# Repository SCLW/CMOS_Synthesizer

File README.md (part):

# CMOS Sound Experimentation Board

*CMOS Sound Experimentation Board. Photo: © Yunfei Zhang.*

## About this project

The board is both a teaching tool and a performance instrument: a low-threshold way to explore audio electronics and logic concepts while also functioning as a working sound source in artistic practice. Inexpensive 4000-series CMOS logic ICs, originally developed for general-purpose digital electronics such as calculators, digital clocks, timing circuits, and industrial control, serve as the sound generators, brought together on a single patchable interface that exposes rather than hides the signal flow. Although the signals are limited to square waves, with no envelopes, no MIDI, and no DSP, the board produces a wide range of sounds and sonic textures.

It was developed within the [Circuitry-Based Sound](https://github.com/SCLW/Circuitry-Based-Sound) seminar at HfG Karlsruhe as part of an ongoing inquiry into how self-built electronics shape experimental sound, collective performance, and arts pedagogy. Many boards have been built, modified, and played in ensemble settings and workshops. That repository documents the broader tradition of CMOS-based sound, related literature, and the underlying electronics.

Technically, the board integrates discrete 4000-series CMOS logic chips on a single PCB that also functions as the user interface. The chips operate as square-wave oscillators, frequency dividers, sequencers, modulators, noise sources, and pattern generators. Prewired connections, selectable switches, and patchable female headers and sockets let users interconnect logic-level signals with jumper wires to explore rhythmic structures, grainy textures, drones, glitches, and complex noise patterns.

---

| **Project Title**     | CMOS Sound Experimentation Board                                                                                                            |
| :-------------------- | :------------------------------------------------------------------------------------------------------------------------------------------ |
| **Hardware Version**      | 2.0 (Rev B; complete 2024 redesign of an earlier 2020 prototype now superseded)                                                   |
| **Documentation Release** | v1.0.0 (first archived release of this repository)                                                                                      |
| **Author / Designer** | Lorenz Schwarz                                                                                                                              |
| **Status**            | Completed                                                                                                                                   |
| **Start Date**        | April 2024                                                                                                                                  |
| **Completion Date**   | May 2024                                                                                                                                    |
| **License**           | [CC BY 4.0](https://creativecommons.org/licenses/by/4.0/)                                                                                   |
| **Description**       | A modular experiment board built around 4000-series CMOS logic chips for sound generation, musical interaction, and circuit-based learning. |
| **Hardware**          | CMOS logic ICs (4000-series), analog multiplexers, potentiometers, slide and rotary switches                                                |
| **Keywords**          | single-PCB, patchable CMOS instrument, educational electronics, experimental sound, logic circuits                                          |

---

## About this documentation

This repository contains all the files and instructions required to build, study, or modify the CMOS Sound Experimentation Board:

- **PCB design files and schematics** (EAGLE)  
- **Assembly and mechanical drawings**  
- **Bill of Materials (BOM)**  
- **Reference tables and component data sheets**

Anyone is free to reproduce, adapt, or extend the instrument for artistic work, performance, or research.

## The instrument

The instrument is designed for hands-on use. Its circuits are prewired for immediate operation but can also be manually interconnected to create new signal paths. All major inputs and outputs are broken out to female headers, allowing flexible patching with male-to-male jumper wires. Global I/O connections make it possible to chain multiple boards together.

The instrument has been used in university seminars, collective performances, and collaborations between electronic and acoustic musicians, from workshops in Langa (Cape Town) to performances at the ZKM Karlsruhe.

*This project is part of the ongoing teaching and research initiative [**Circuitry-Based Sound**](https://github.com/SCLW/Circuitry-Based-Sound) at the HfG Karlsruhe, which explores the relationship between electronic circuitry, interaction, and sound.*

*CMOS Sound Experimentation Board. Photo: © Tobias Ehrhardt.*

## Performances and contexts of use

The board has been used as a shared platform across the Circuitry-Based Sound programme since 2024, including:

- **ng X, next_generation X festival**, ZKM, Karlsruhe (2024)
- **Workshop with Dizu Plaatjies**, Langa, Cape Town, South Africa (2024)
- **Bowed Electrons / IMMP**, !Khwa ttu San Heritage Centre, South Africa (2024)
- **Open M Art Fair**, OōEli Hangzhou Tianmuli, Hangzhou (2025)
- **SAE Cape Town workshop**, Cape Town, South Africa (2025)
- **MKULTRA Sound 2026**, HfG Karlsruhe (2026)

Boards built by participants have been used in solo and ensemble configurations, patched together via the chained clock and external-input headers. Demo video and context: <https://medienkunst-sound.de/works/cmos-synthesizer>.

---

*Circuitry-Based Sound participants preparing for the* next_generation X *festival performance in the ZKM Klangdom, Karlsruhe, 2024. Photo: © Hongyu Guo.*

<br>

*Workshop with Dizu Plaatjies in Langa, Cape Town, South Africa, 2024. Participants assemble and patch their CMOS Sound Experimentation Boards through portable amplifiers. Photo: © Paul Modler.*

<br>

*Bowed Electrons / IMMP, !Khwa ttu San Heritage Centre, South Africa, 2024. A performer operates the CMOS Sound Experimentation Board during the concert; other musicians prepare in the background. Photo: © Clive Pringle.*

<br>

*Visitors inspecting the CMOS Sound Experimentation Board at the Open M Art Fair, OōEli Hangzhou Tianmuli, China, 2025. Photo: © Yunfei Zhang.*

<br>

*Circuitry-Based Sound workshop at SAE Cape Town, with participants working on the boards, 2025. Photo: © Paul Modler.*

<br>

*MKULTRA Sound 2026, audiovisual performance by Yunfei Zhang and Xinyun Zhang at HfG Karlsruhe, February 2026. The board controls a hacked VGA video signal generator while simultaneously functioning as a sound source. Photo: © Jihye Gebhart.*

<br>

*Live-generated VGA visual projected on a wall at HfG Karlsruhe during the same MKULTRA Sound 2026 performance by Xinyun Zhang and Yunfei Zhang. Photo: © Jihye Gebhart.*

## Disclaimer

This material is for educational and research purposes. Although prepared with care, errors may remain. Building this synthesizer may require additional knowledge/experience in electronics and prototyping. The materials are provided to encourage exploration and adaptation.

---

### Specifications

- **PCB:** custom 2-layer board
- **Dimensions (Board):** 278 mm × 186 mm  
- **Dimensions (Populated + Base Plate):** 284 mm × 192 mm × 35 mm
- **Power Requirements:** Operating range 9–18 V DC; recommended 9–12 V (typical 9 V battery). The oscillator frequency-range table in the [Appendix](#appendix) is calibrated at 10 V.
- **Component Types:**
  - **ICs:** CMOS 4000-series; mix of SMD and through-hole
  - **Passives:** SMD resistors (0805), SMD ceramic/electrolytic capacitors
  - **Electromechanical:** vertical PCB-mount potentiometers; slide/rotary switches (THT); 2.54 mm pin headers & sockets
- **Audio:**
  - Mono output, ~4 Vpp typical; up to synth/modular level with gains fully open
  - Master output pot provides attenuation toward line level
- **Connectors:**
  - **Power in:** 2-pin male header (2.54 mm); polarity marked on PCB silkscreen; mating cable: 2-pos female socket → wire leads (~600 mm)
  - **Audio out:** 3.5 mm mono jack
  - **Expansion/control:** 2.54 mm female headers (various pin counts) for patching

---

## Circuit Elements on the CMOS Sound Experimentation Board

The board integrates a wide range of CMOS logic-based sound circuits, allowing direct experimentation with square-wave oscillators, counters, modulators, sequencers, and switches. All elements are accessible via female headers and can be interconnected using jumper wires to create complex rhythmic and sonic structures.

In total the board offers up to **13 oscillator positions**: 8 gated oscillators based on CD4093 (sections 1–8 below), 4 sensor-input oscillators based on CD40106 (sections 9–12), and 1 master clock (also CD40106, described as its own section).

<picture>
  <source media="(prefers-color-scheme: dark)" srcset="/assets/img/overlay-functions-dark.svg">
  
</picture>

Functional diagram of the CMOS Sound Experimentation Board, showing the main circuit sections and their interconnections.

### GATED OSCILLATORS 1-8 [2×]

Each of the two sections contains four gated Schmitt-trigger oscillators based on the CD4093 NAND gate IC.
These circuits generate square-wave signals, each with its own frequency potentiometer, range selector, and logic gate input for gating or modulation.

### XOR MODULATOR [2×]

Two XOR-based square-wave modulators (CD4070) for logical ring modulation to create new harmonic relationships. Each modulated output is individually accessible and can be patched into other sections.

### SWITCH 1 OF 8 [2×]

Two CD4051 analog MUX/DEMUX sections acting as 1-of-8 selectors. Selection via three logic inputs, optionally driven by a CD4024 binary counter (0–7) to step through the switch positions automatically. The switch operates bidirectionally: it can either route one signal to one of eight destinations or select one of eight inputs to a common output.

### SWITCH 3 × 1 OF 2 [1×]

Built around a CD4053 triple SPDT analog switch, this circuit provides three independent 2-channel selectors. Each channel can switch between two input signals under binary logic control, which requires an additional logic control input. The switch operates bidirectionally: it can either route one signal to one of two destinations or select one of two inputs to a common output.

### FREQUENCY DIVIDER [2×]

Two 7-stage binary counters (CD4024) used as binary number generators (÷2…÷128). One pre-clocked from gated oscillator #8; the other can receive any selectable clock source via a rotary switch.

### SEQUENCER/COUNTER [1×]

Based on CD4022, an 8-stage Johnson counter acting as a step sequencer. It outputs sequential logic pulses across eight decoded outputs and includes a reset function. The sequencer clock can be selected via a rotary switch.

### DIVIDE BY 3, 5, 7, 9 [1×]

A divide-by-odd “pattern generator” implemented using CD4018 and CD4011. It generates rhythmic subdivisions by dividing the input clock into odd-numbered ratios (÷3, ÷5, ÷7, ÷9). The clock source is selectable through one of the rotary switches.

### OSCILLATORS 9–12

Four auxiliary Schmitt-trigger oscillators (CD40106) with sockets for touch, light-dependent, or resistive sensors. These share the same CD40106 IC as the master clock (see [Clock](#clock-1) below); inserting a variable resistor or sensor into the open pads activates each oscillator.

### CLOCK [1×]

One of the CD40106 Schmitt trigger inverters is configured as the master clock oscillator. The clock signal is routed via the rotary switches, allowing it to be assigned as a timing source to different logic sections, and can additionally be sent to an external output for synchronization between multiple boards.

### PSEUDO RANDOM NUMBER GENERATOR [1×]

Based on three interconnected CD4094 shift registers (24 stages) forming a linear-feedback shift register (LFSR). The circuit generates pseudo-random bit patterns and requires an additional adapter board for seeding and deadlock-prevention circuit using CD4068, CD4070, and CD4077 to ensure continuous operation. See [LFSR Deadlock Prevention Circuit](#lfsr-deadlock-prevention-circuit-required). The clock source can be selected via one of the rotary switches.

### MIXER [1×]

4-channel summing amplifier (LM358) with per-channel gain and master level. The mixed signal is available as mono output.

### ROTARY SWITCHES [3x]

Three Single Pole, 8-Throw rotary switches (SP8T) provide manual routing of oscillator and clock signals to different logic sections. Each switch selects one of eight possible sources, allowing flexible assignment of timing and modulation signals across the system.

| **Position** | **Source**       |
| :----------: | :--------------- |
|       1      | OSC1             |
|       2      | OSC2             |
|       3      | OSC3             |
|       4      | OSC4             |
|       5      | Master Clock     |
|       6      | OSC8 ÷ 4         |
|       7      | External Input 1 |
|       8      | External Input 2 |

---

## Schematics & design files

Complete circuit schematics (PDF) for all sections are in [`/assets/exports/`](./assets/exports/).  
Editable EAGLE design files are in [`/assets/pcb/`](./assets/pcb/).  
For a browsable SVG overview that links to PDFs, see [`/assets/exports/README.md`](./assets/exports/README.md).

> **Note on EAGLE.** The `.brd` and `.sch` files were created with Autodesk EAGLE (last standalone release 9.6.2, now discontinued). They can still be opened in Autodesk Fusion's Electronics workspace, or imported into KiCad via its built-in EAGLE importer.

## Build guide

The main PCB integrates all control elements (potentiometers, toggle switches, tactile buttons) directly. No separate front panel or off-board wiring is needed. One auxiliary add-on PCB prevents LFSR deadlock and mounts directly on the main board; see [LFSR Deadlock Prevention Circuit](#lfsr-deadlock-prevention-circuit-required).

## The main board

*CAM top view of the main board showing component outlines, silkscreen labels and pad holes.*  

**Main Board with component outline**  

*Top view of the main PCB showing component outlines and mounting holes. This overlay provides a visual reference for component placement.*

<details>

<summary>PCB Reference Designators and Component List, main board (click to expand)</summary>

> This table lists the components for the **main board only**. The LFSR deadlock-prevention add-on has its own component list further down ([here](#lfsr-deadlock-prevention-circuit-required)) and its own entry in the [BOM file](/assets/bom/README.md#lfsr-deadlock-prevention-add-on-board).

| Qty    | Value          | Package     | Designators                                         | Description                                  |
| ------ | -------------- | ----------- | --------------------------------------------------- | -------------------------------------------- |
| 1      | 1 kΩ           | R0805       | R23                                                 | SMD Resistor                                 |
| 10     | 2.7 kΩ         | R0805       | R1–R8, R13, R15                                     | SMD Resistor                                 |
| 1      | 150 kΩ         | R0805       | R26                                                 | SMD Resistor                                 |
| 7      | 10 kΩ          | R0805       | R14, R16–R20, R27                                   | SMD Resistor                                 |
| 8      | 100 kΩ         | R0805       | R9–R12, R21–R22, R24–R25                            | SMD Resistor                                 |
| 15     | 10 µF          | PANASONIC_D | C1–C7, C12–C13, C23, C49–C53                        | Electrolytic Capacitor (SMD; C23 optional, depends on master-clock timing choice) |
| 36     | 0.1 µF         | C0805       | C8–C11, C14–C17, C18–C22, C24–C29, C31–C41, C43–C48 | SMD Ceramic Capacitor                        |
| 14     | 100 kΩ         | POT_VER     | U$1–U$14                                            | Potentiometer, vertical                      |
| 2      | —              |             | S12–S13                                             | Tactile pushbutton (momentary, SMD)          |
| 8      | —              | THT         | S1–S8                                               | Toggle Switch, ON–ON                         |
| 1      | CD40106        | DIL14       | IC13                                                | Hex Schmitt Trigger Inverter                 |
| 1      | CD4011         | DIL14       | IC12                                                | Quad 2-input NAND                            |
| 1      | CD4018         | DIL16       | IC11                                                | Counter / Divider                            |
| 1      | CD4022         | DIL16       | IC9                                                 | Divide-by-8 Counter                          |
| 2      | CD4024         | DIL14       | IC6, IC8                                            | 7-stage Binary / Ripple Counter              |
| 2      | CD4051         | DIL16       | IC2, IC5                                            | 8-channel Analog Multiplexer                 |
| 1      | CD4053         | DIL16       | IC7                                                 | Triple 2-channel Analog Multiplexer          |
| 2      | CD4070         | DIL14       | IC4, IC14 (IC18 unpopulated)                        | Quad 2-input XOR                             |
| 2      | CD4093         | DIL14       | IC1, IC3                                            | Quad 2-input NAND Schmitt Trigger            |
| 3      | CD4094         | DIL16       | IC15–IC17                                           | 8-stage Shift Register                       |
| 1      | LM358          | DIL08       | IC10                                                | Dual Operational Amplifier                   |
| 1      | MBRS1540       |             | D1                                                  | Schottky Protection Diode (1.5 A / 40 V)     |
| 1      | MJ-3523-SMT-TR | SMD         | —                                                   | Female Jack Connector, 3.5 mm, surface-mount |
| 3      | —              | ROTARY      | S9–S11                                              | Rotary Switch                                |
| 8      | —              | DIL14       | —                                                   | IC Socket                                    |
| 1      | —              | DIL08       | —                                                   | IC Socket                                    |
| 8      | —              | DIL16       | —                                                   | IC Socket                                    |
| 5      | —              | 1×8 2.54    | —                                                   | Female Header                                |
| 2      | —              | 1×3 2.54    | —                                                   | Female Header                                |
| 1      | —              | 1×6 2.54    | —                                                   | Female Header                                |
| 6      | —              | 1×2 2.54    | —                                                   | Female Header                                |
| 1      | —              | 1×5 2.54    | —                                                   | Female Header                                |
| 2      | —              | 1×7 2.54    | —                                                   | Female Header                                |
| 11     | —              | 1×4 2.54    | —                                                   | Female Header                                |
| 1      | —              | 1×9 2.54    | —                                                   | Female Header                                |
| 4      | —              | 2×4 2.54    | —                                                   | Female Header                                |
| 1      | —              | 2×3 2.54    | —                                                   | Female Header                                |
| 4      | —              | 1×2 2.54    | —                                                   | Pin Header (Male)                            |

C1, C3–C7, C8–C11, C12–C13, C14–C17, C18–C21, C23, and C25–C29 act as timing capacitors for the Schmitt-trigger RC oscillators in combination with their corresponding resistors. These values can be substituted to tailor the oscillator frequency ranges (see frequency table).

</details>

### Assembly order

The following is a suggested sequence that outlines the build order without step-by-step detail. Refer to the schematics in `/assets/exports/` and the board overlays above for orientation and placement.

1. **Main PCB**
   1) SMD resistors  
   2) SMD capacitors (see [Appendix](#appendix))  
   3) IC sockets  
   4) ICs  
   5) Controls (potentiometers & switches)  
   6) Connectors (2.54 mm headers & sockets)

   **Important:** Do not solder the headers on the main board where the LFSR deadlock-prevention adapter will later be mounted. Solder these headers only on the adapter board, then plug into the main board.

2. **Audio output adapter (obsolete)**
   - For historical reference only; no longer required for audio output in 2024 revision.

3. **Deadlock prevention board for PRNG/LFSR circuit (required)**
   - Three 1×8 female headers + one 1×3 female header to the main board  
   - Two additional wires for VCC and GND

4. **Mechanical assembly**
   - Mount main PCB on acrylic base plate using 8 spacers and M3 screws  

## Modifications and add-on boards

### Audio output adapter (obsolete)
Earlier revisions required a small mono audio adapter (SMT 3.5 mm jack on a daughterboard).  
In the 2024 revision B, the audio section is fixed on the main PCB.

### LFSR Deadlock Prevention Circuit (required)

*CAM top view of the deadlock prevention add-on PCB.*

The LFSR can lock in an all-ones state. A small SMD add-on (CD4068, CD4070, CD4077) detects the static state and injects a seed pulse. It connects to the main board via three 1×8 and one 1×3 female headers, and requires two additional wires for power (VCC and GND).

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
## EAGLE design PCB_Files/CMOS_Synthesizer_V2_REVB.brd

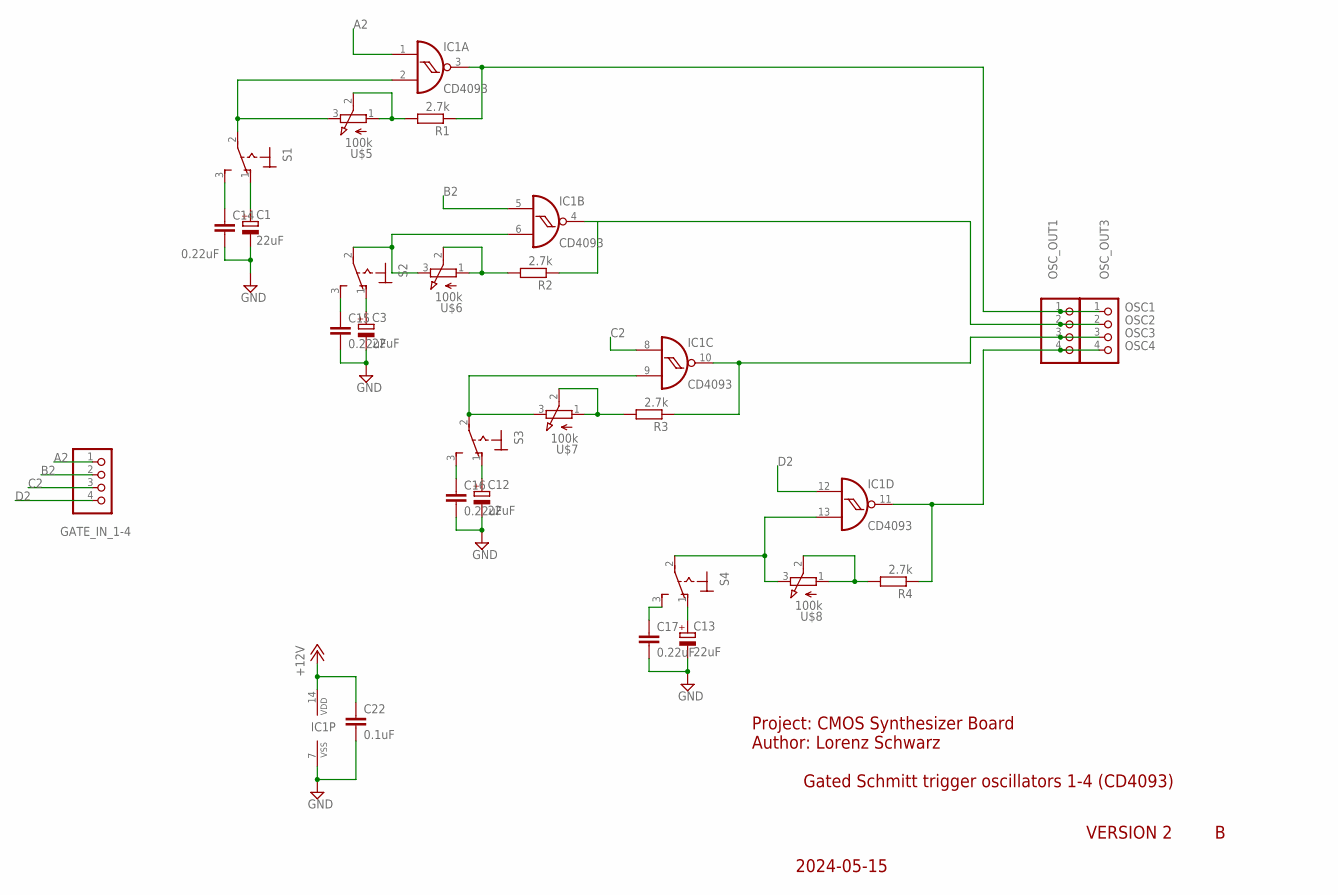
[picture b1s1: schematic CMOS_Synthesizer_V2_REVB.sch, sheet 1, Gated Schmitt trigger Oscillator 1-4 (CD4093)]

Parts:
C1, C3, C12, C13: 22uF; PANASONIC_D
C14, C15, C16, C17: 0.22uF; C0805
C22: 0.1uF; C0805
GATE_IN_1-4: PINHD-1X4_2.54; 1X04
IC1: CD4093; DIL14
OSC_OUT1, OSC_OUT3: PINHD-1X4_2.54; 1X04
R1, R2, R3, R4: 2.7k; R0805
S1, S2, S3, S4: M9040P
U$5, U$6, U$7, U$8: 100k; POT_VER

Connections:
+12V: C22.1, IC1.14 (VDD); also elsewhere on the board
A2: GATE_IN_1-4.1, IC1.1 (I0)
B2: GATE_IN_1-4.2, IC1.5 (I0)
C2: GATE_IN_1-4.3, IC1.8 (I0)
D2: GATE_IN_1-4.4, IC1.12 (I0)
GND: C1.-, C3.-, C12.-, C13.-, C14.2, C15.2, C16.2, C17.2, C22.2, IC1.7 (VSS); also elsewhere on the board
unnamed: C1.+, S1.1 (O)
unnamed: IC1.2 (I1), S1.2, U$5.3 (E)
unnamed: C3.+, S2.1 (O)
unnamed: C15.1, S2.3 (S)
unnamed: IC1.6 (I1), S2.2, U$6.3 (E)
unnamed: C12.+, S3.1 (O)
unnamed: C16.1, S3.3 (S)
unnamed: IC1.9 (I1), S3.2, U$7.3 (E)
unnamed: C13.+, S4.1 (O)
unnamed: C17.1, S4.3 (S)
unnamed: IC1.13 (I1), S4.2, U$8.3 (E)
unnamed: R1.2, U$5.1 (A), U$5.2 (S)
unnamed: R2.2, U$6.1 (A), U$6.2 (S)
unnamed: R3.2, U$7.1 (A), U$7.2 (S)
unnamed: R4.2, U$8.1 (A), U$8.2 (S)
unnamed: C14.1, S1.3 (S)
OSC1: IC1.3 (O), OSC_OUT1.1, OSC_OUT3.1, R1.1; also elsewhere on the board
OSC2: IC1.4 (O), OSC_OUT1.2, OSC_OUT3.2, R2.1; also elsewhere on the board
OSC3: IC1.10 (O), OSC_OUT1.3, OSC_OUT3.3, R3.1; also elsewhere on the board
OSC4: IC1.11 (O), OSC_OUT1.4, OSC_OUT3.4, R4.1; also elsewhere on the board

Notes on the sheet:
Project: CMOS Synthesizer Board Author: Lorenz Schwarz
Gated Schmitt trigger oscillators 1-4 (CD4093)
2024-05-15
VERSION 2

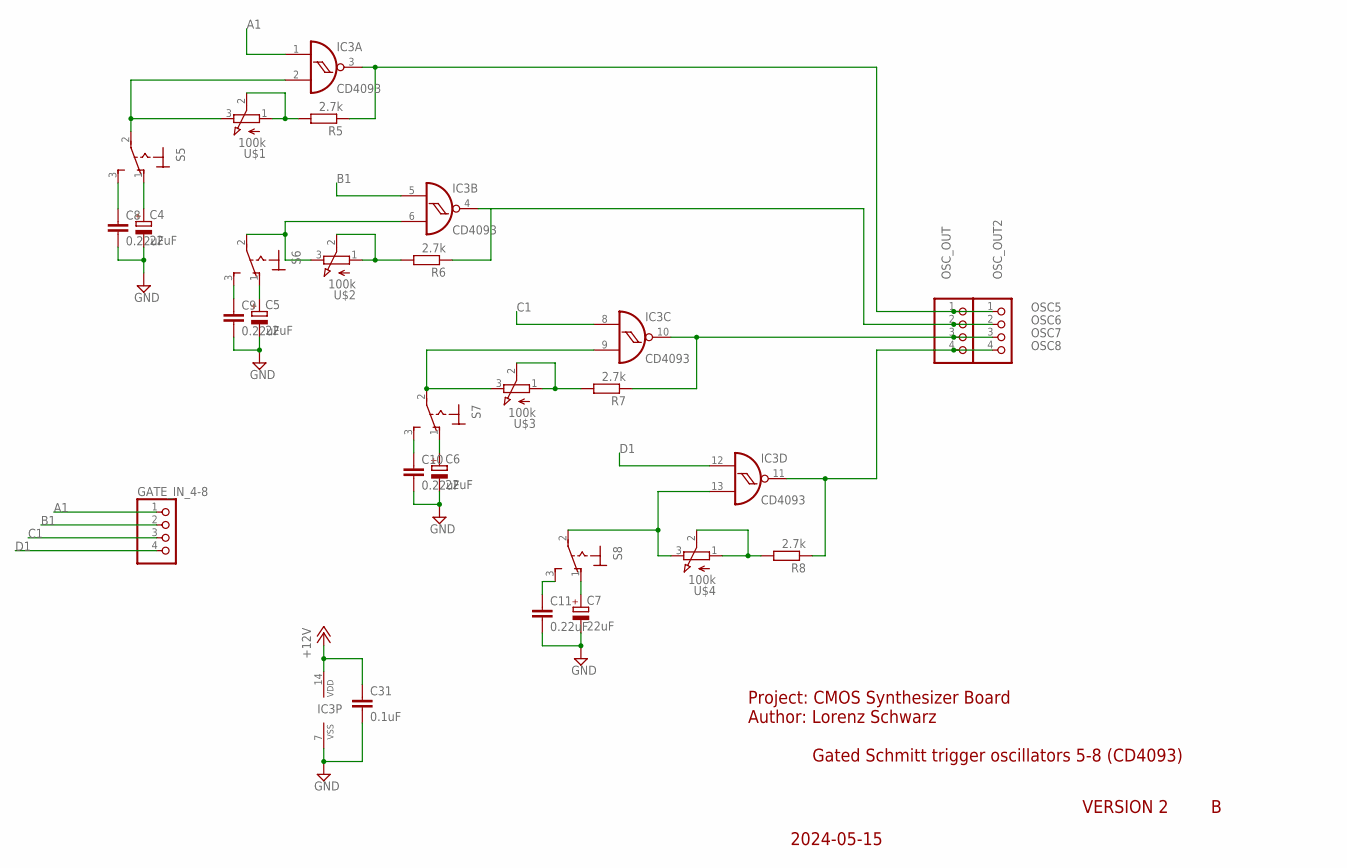
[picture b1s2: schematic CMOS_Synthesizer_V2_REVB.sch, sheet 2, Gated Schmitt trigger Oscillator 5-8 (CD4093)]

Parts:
C4, C5, C6, C7: 22uF; PANASONIC_D
C8, C9, C10, C11: 0.22uF; C0805
C31: 0.1uF; C0805
GATE_IN_4-8: PINHD-1X4_2.54; 1X04
IC3: CD4093; DIL14
OSC_OUT, OSC_OUT2: PINHD-1X4_2.54; 1X04
R5, R6, R7, R8: 2.7k; R0805
S5, S6, S7, S8: M9040P
U$1, U$2, U$3, U$4: 100k; POT_VER

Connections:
+12V: C31.1, IC3.14 (VDD); also elsewhere on the board
A1: GATE_IN_4-8.1, IC3.1 (I0)
B1: GATE_IN_4-8.2, IC3.5 (I0)
C1: GATE_IN_4-8.3, IC3.8 (I0)
D1: GATE_IN_4-8.4, IC3.12 (I0)
GND: C4.-, C5.-, C6.-, C7.-, C8.2, C9.2, C10.2, C11.2, C31.2, IC3.7 (VSS); also elsewhere on the board
unnamed: C5.+, S6.1 (O)
unnamed: C9.1, S6.3 (S)
unnamed: C8.1, S5.3 (S)
unnamed: C4.+, S5.1 (O)
unnamed: IC3.2 (I1), S5.2, U$1.3 (E)
unnamed: IC3.6 (I1), S6.2, U$2.3 (E)
unnamed: C6.+, S7.1 (O)
unnamed: C10.1, S7.3 (S)
unnamed: IC3.9 (I1), S7.2, U$3.3 (E)
unnamed: C7.+, S8.1 (O)
unnamed: C11.1, S8.3 (S)
unnamed: IC3.13 (I1), S8.2, U$4.3 (E)
unnamed: R5.2, U$1.1 (A), U$1.2 (S)
unnamed: R6.2, U$2.1 (A), U$2.2 (S)
unnamed: R7.2, U$3.1 (A), U$3.2 (S)
unnamed: R8.2, U$4.1 (A), U$4.2 (S)
OSC5: IC3.3 (O), OSC_OUT.1, OSC_OUT2.1, R5.1
OSC6: IC3.4 (O), OSC_OUT.2, OSC_OUT2.2, R6.1
OSC7: IC3.10 (O), OSC_OUT.3, OSC_OUT2.3, R7.1
OSC8: IC3.11 (O), OSC_OUT.4, OSC_OUT2.4, R8.1; also elsewhere on the board

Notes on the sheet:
Project: CMOS Synthesizer Board Author: Lorenz Schwarz
Gated Schmitt trigger oscillators 5-8 (CD4093)
2024-05-15
VERSION 2

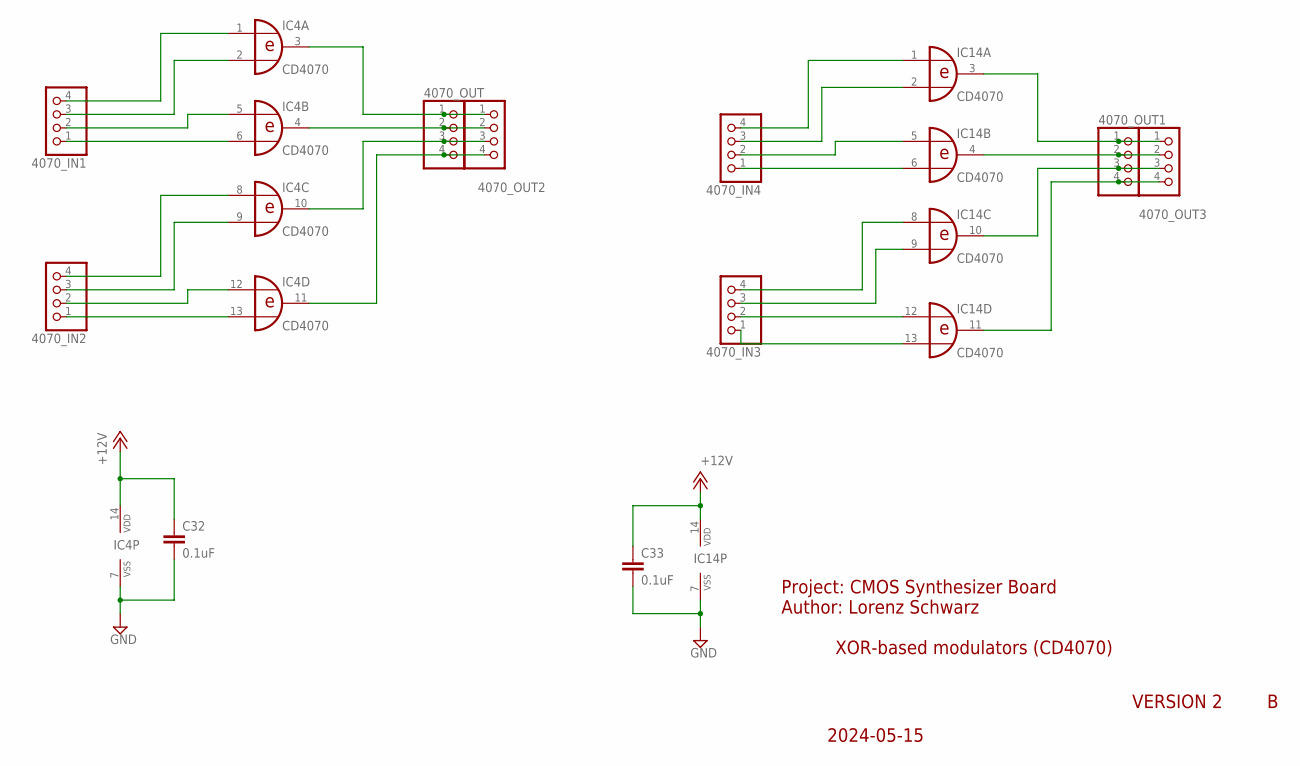
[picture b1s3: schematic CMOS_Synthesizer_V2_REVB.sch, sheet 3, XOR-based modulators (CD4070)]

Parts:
4070_IN1, 4070_IN2, 4070_IN3, 4070_IN4, 4070_OUT, 4070_OUT1, 4070_OUT2, 4070_OUT3: PINHD-1X4_2.54; 1X04
C32, C33: 0.1uF; C0805
IC4, IC14: CD4070; DIL14

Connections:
+12V: C32.1, C33.1, IC4.14 (VDD), IC14.14 (VDD); also elsewhere on the board
GND: C32.2, C33.2, IC4.7 (VSS), IC14.7 (VSS); also elsewhere on the board
unnamed: 4070_OUT.1, 4070_OUT2.1, IC4.3 (O)
unnamed: 4070_OUT.2, 4070_OUT2.2, IC4.4 (O)
unnamed: 4070_OUT.3, 4070_OUT2.3, IC4.10 (O)
unnamed: 4070_OUT.4, 4070_OUT2.4, IC4.11 (O)
unnamed: 4070_IN1.4, IC4.1 (I0)
unnamed: 4070_IN1.3, IC4.2 (I1)
unnamed: 4070_IN1.2, IC4.5 (I0)
unnamed: 4070_IN1.1, IC4.6 (I1)
unnamed: 4070_IN2.4, IC4.8 (I0)
unnamed: 4070_IN2.3, IC4.9 (I1)
unnamed: 4070_IN2.2, IC4.12 (I0)
unnamed: 4070_IN2.1, IC4.13 (I1)
unnamed: 4070_OUT1.1, 4070_OUT3.1, IC14.3 (O)
unnamed: 4070_OUT1.2, 4070_OUT3.2, IC14.4 (O)
unnamed: 4070_OUT1.3, 4070_OUT3.3, IC14.10 (O)
unnamed: 4070_OUT1.4, 4070_OUT3.4, IC14.11 (O)
unnamed: 4070_IN4.4, IC14.1 (I0)
unnamed: 4070_IN4.3, IC14.2 (I1)
unnamed: 4070_IN4.2, IC14.5 (I0)
unnamed: 4070_IN4.1, IC14.6 (I1)
unnamed: 4070_IN3.4, IC14.8 (I0)
unnamed: 4070_IN3.3, IC14.9 (I1)
unnamed: 4070_IN3.2, IC14.12 (I0)
unnamed: 4070_IN3.1, IC14.13 (I1)

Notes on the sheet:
Project: CMOS Synthesizer Board Author: Lorenz Schwarz
XOR-based modulators (CD4070)
2024-05-15
VERSION 2

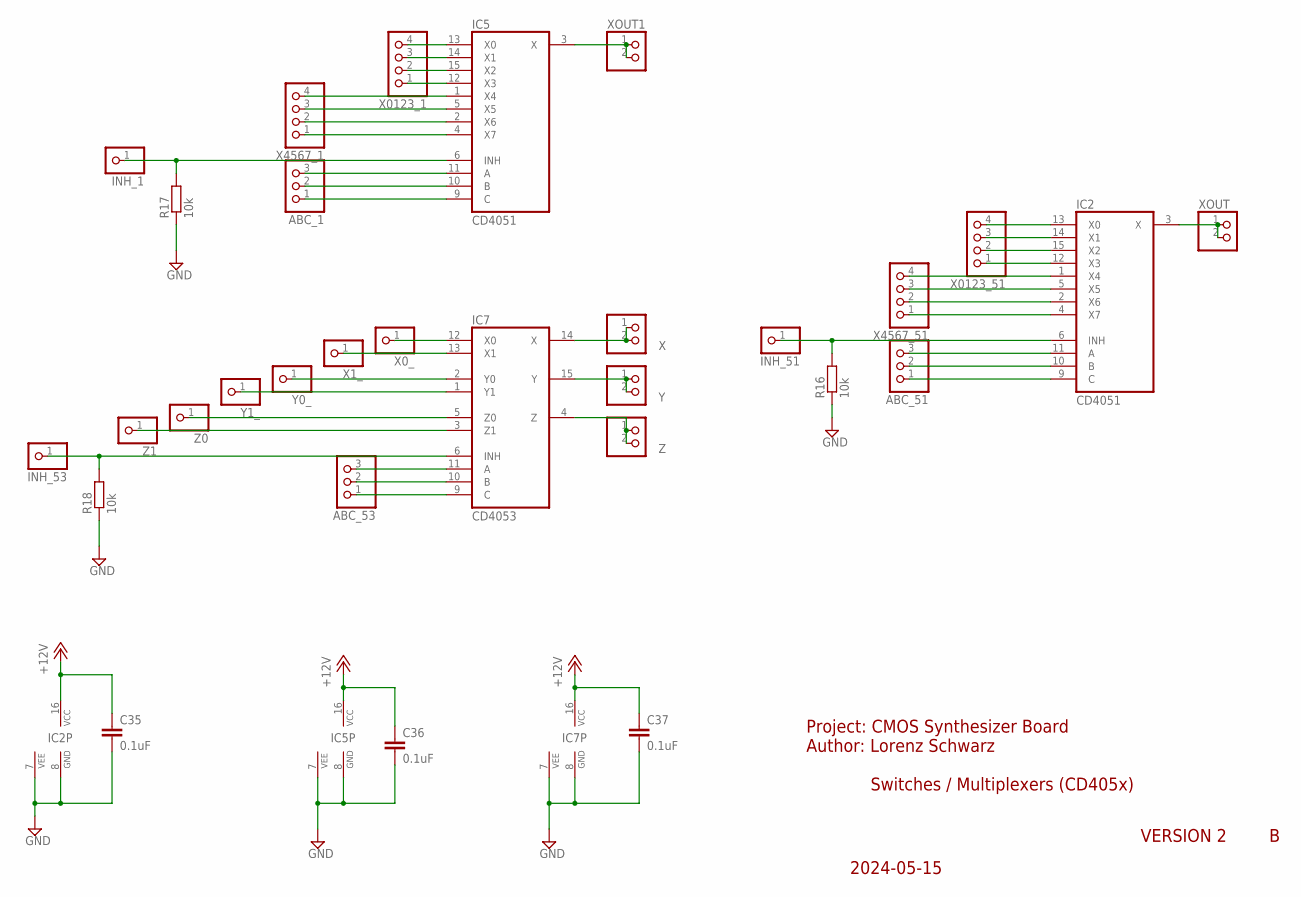
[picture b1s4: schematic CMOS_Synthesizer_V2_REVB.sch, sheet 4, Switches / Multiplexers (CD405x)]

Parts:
ABC_1, ABC_51, ABC_53: PINHD-1X3; 1X03
C35, C36, C37: 0.1uF; C0805
IC2, IC5: CD4051; DIL16
IC7: CD4053; DIL16
INH_1, INH_51, INH_53: PINHD-1X1; 1X01
R16, R17, R18: 10k; R0805
X: PINHD-1X2; 1X02
X0_, X1_: PINHD-1X1; 1X01
X0123_1, X0123_51, X4567_1, X4567_51: PINHD-1X4_2.54; 1X04
XOUT, XOUT1: PINHD-1X2; 1X02
Y: PINHD-1X2; 1X02
Y0_, Y1_: PINHD-1X1; 1X01
Z: PINHD-1X2; 1X02
Z0, Z1: PINHD-1X1; 1X01

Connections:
+12V: C35.1, C36.1, C37.1, IC2.16 (VCC), IC5.16 (VCC), IC7.16 (VCC); also elsewhere on the board
GND: C35.2, C36.2, C37.2, IC2.7 (VEE), IC2.8 (GND), IC5.7 (VEE), IC5.8 (GND), IC7.7 (VEE), IC7.8 (GND), R16.1, R17.1, R18.1; also elsewhere on the board
unnamed: IC5.12 (X3), X0123_1.1
unnamed: IC5.15 (X2), X0123_1.2
unnamed: IC5.14 (X1), X0123_1.3
unnamed: IC5.13 (X0), X0123_1.4
unnamed: IC7.4 (Z), Z.1, Z.2
unnamed: IC7.15 (Y), Y.1, Y.2
unnamed: IC7.14 (X), X.1, X.2
unnamed: IC7.6 (INH), INH_53.1, R18.2
unnamed: ABC_53.1, IC7.9 (C)
unnamed: ABC_53.2, IC7.10 (B)
unnamed: ABC_53.3, IC7.11 (A)
unnamed: IC7.13 (X1), X1_.1
unnamed: IC5.4 (X7), X4567_1.1
unnamed: IC7.12 (X0), X0_.1
unnamed: IC7.1 (Y1), Y1_.1
unnamed: IC7.2 (Y0), Y0_.1
unnamed: IC7.3 (Z1), Z1.1
unnamed: IC7.5 (Z0), Z0.1
unnamed: IC5.2 (X6), X4567_1.2
unnamed: IC5.5 (X5), X4567_1.3
unnamed: IC5.1 (X4), X4567_1.4
unnamed: IC5.6 (INH), INH_1.1, R17.2
unnamed: ABC_1.1, IC5.9 (C)
unnamed: ABC_1.2, IC5.10 (B)
unnamed: ABC_1.3, IC5.11 (A)
unnamed: IC5.3 (X), XOUT1.1, XOUT1.2
unnamed: IC2.12 (X3), X0123_51.1
unnamed: IC2.15 (X2), X0123_51.2
unnamed: IC2.14 (X1), X0123_51.3
unnamed: IC2.13 (X0), X0123_51.4
unnamed: IC2.4 (X7), X4567_51.1
unnamed: IC2.2 (X6), X4567_51.2
unnamed: IC2.5 (X5), X4567_51.3
unnamed: IC2.1 (X4), X4567_51.4
unnamed: IC2.6 (INH), INH_51.1, R16.2
unnamed: ABC_51.1, IC2.9 (C)
unnamed: ABC_51.2, IC2.10 (B)
unnamed: ABC_51.3, IC2.11 (A)
unnamed: IC2.3 (X), XOUT.1, XOUT.2

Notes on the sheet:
Project: CMOS Synthesizer Board Author: Lorenz Schwarz
Switches / Multiplexers (CD405x)
2024-05-15
VERSION 2

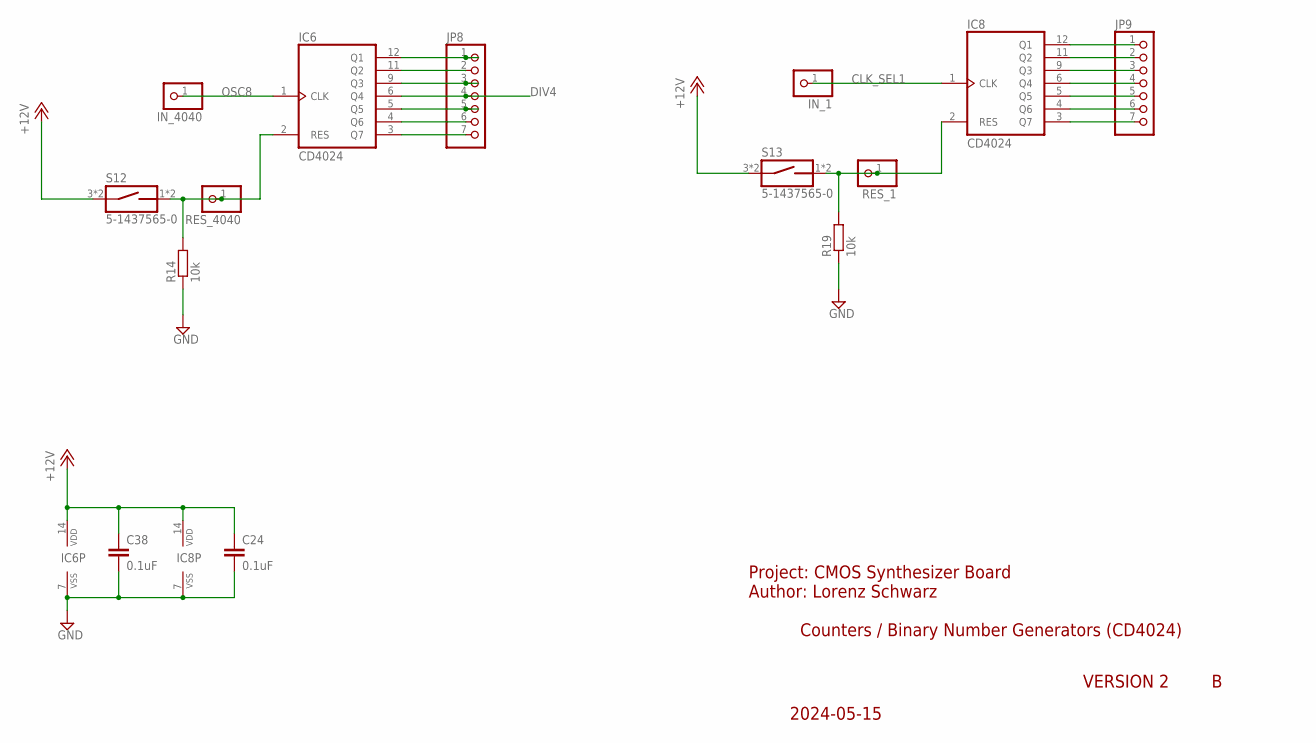
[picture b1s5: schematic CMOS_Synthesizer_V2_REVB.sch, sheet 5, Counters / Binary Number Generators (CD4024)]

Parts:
C24, C38: 0.1uF; C0805
IC6, IC8: CD4024; DIL14
IN_1, IN_4040: PINHD-1X1; 1X01
JP8, JP9: PINHD-1X7; 1X07
R14, R19: 10k; R0805
RES_1, RES_4040: PINHD-1X1; 1X01
S12, S13: 5-1437565-0; SW_5-1437565-0

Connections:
+12V: C24.1, C38.1, IC6.14 (VDD), IC8.14 (VDD), S12.3 (1), S12.4 (1), S13.3 (1), S13.4 (1); also elsewhere on the board
CLK_SEL1: IC8.1 (CLK), IN_1.1; also elsewhere on the board
DIV4: IC6.6 (Q4), JP8.4; also elsewhere on the board
GND: C24.2, C38.2, IC6.7 (VSS), IC8.7 (VSS), R14.1, R19.1; also elsewhere on the board
unnamed: IC6.11 (Q2), JP8.2
unnamed: IC8.12 (Q1), JP9.1
unnamed: IC8.11 (Q2), JP9.2
unnamed: IC8.9 (Q3), JP9.3
unnamed: IC6.4 (Q6), JP8.6
unnamed: IC6.12 (Q1), JP8.1
unnamed: IC6.9 (Q3), JP8.3
unnamed: IC6.5 (Q5), JP8.5
unnamed: IC6.3 (Q7), JP8.7
unnamed: IC8.6 (Q4), JP9.4
unnamed: IC6.2 (RES), R14.2, RES_4040.1, S12.1 (2), S12.2
unnamed: IC8.5 (Q5), JP9.5
unnamed: IC8.4 (Q6), JP9.6
unnamed: IC8.3 (Q7), JP9.7
unnamed: IC8.2 (RES), R19.2, RES_1.1, S13.1 (2), S13.2
OSC8: IC6.1 (CLK), IN_4040.1; also elsewhere on the board

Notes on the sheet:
Project: CMOS Synthesizer Board Author: Lorenz Schwarz
Counters / Binary Number Generators (CD4024)
2024-05-15
VERSION 2

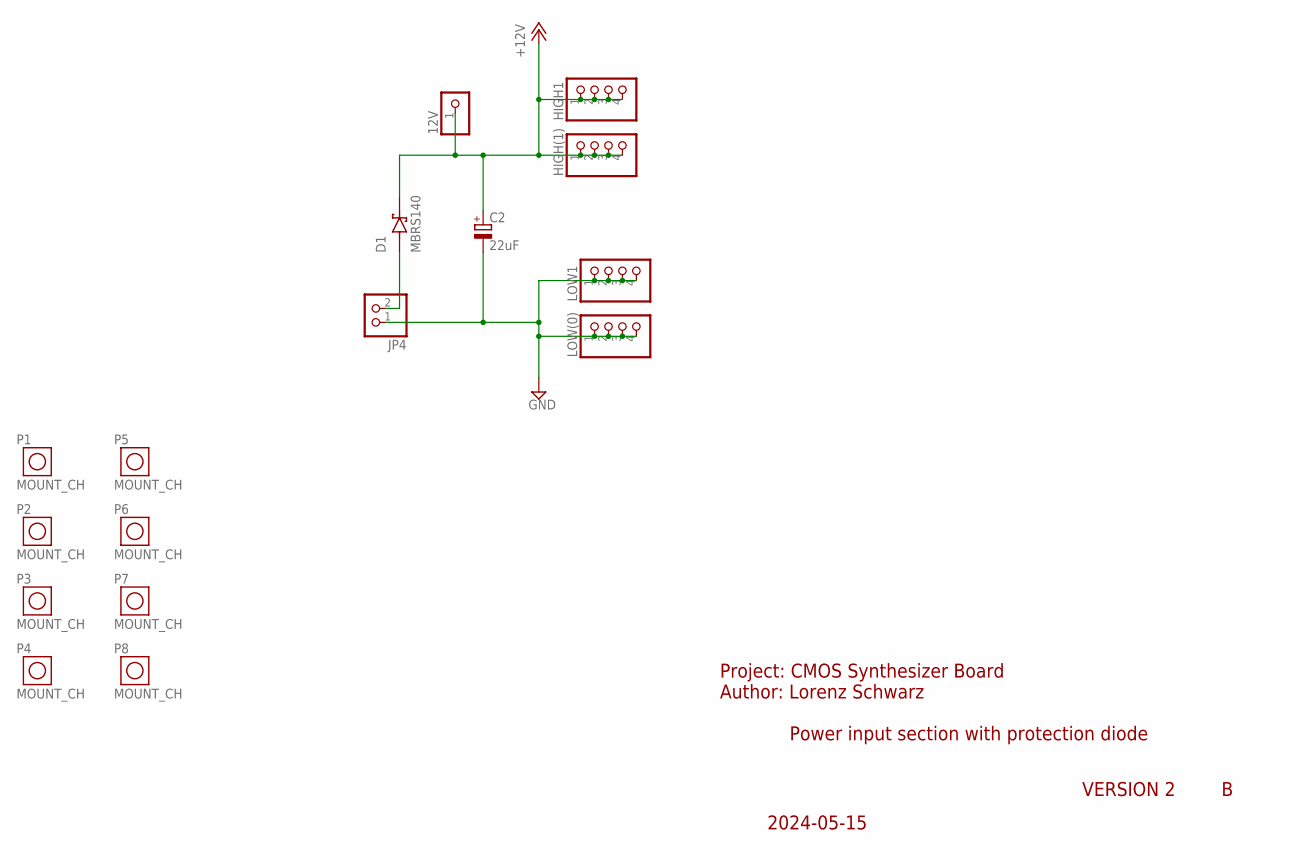
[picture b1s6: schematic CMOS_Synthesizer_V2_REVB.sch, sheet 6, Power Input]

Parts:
12V: PINHD-1X1; 1X01
C2: 22uF; PANASONIC_D
D1: MBRS140; DIO_MBRS140
HIGH1: PINHD-1X4; 1X04
HIGH(1): PINHD-1X4; 1X04
JP4: PINHD-1X2_2.54; 1X02
LOW1: PINHD-1X4; 1X04
LOW(0): PINHD-1X4; 1X04
P1, P2, P3, P4, P5, P6, P7, P8: MOUNT_CH; MOUNT_CH32

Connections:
+12V: 12V.1, C2.+, D1.C (K), HIGH1.1, HIGH1.2, HIGH1.3, HIGH1.4, HIGH(1).1, HIGH(1).2, HIGH(1).3, HIGH(1).4; also elsewhere on the board
GND: C2.-, JP4.1, LOW1.1, LOW1.2, LOW1.3, LOW1.4, LOW(0).1, LOW(0).2, LOW(0).3, LOW(0).4; also elsewhere on the board
unnamed: D1.A, JP4.2

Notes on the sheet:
Project: CMOS Synthesizer Board Author: Lorenz Schwarz
Power input section with protection diode
2024-05-15
VERSION 2

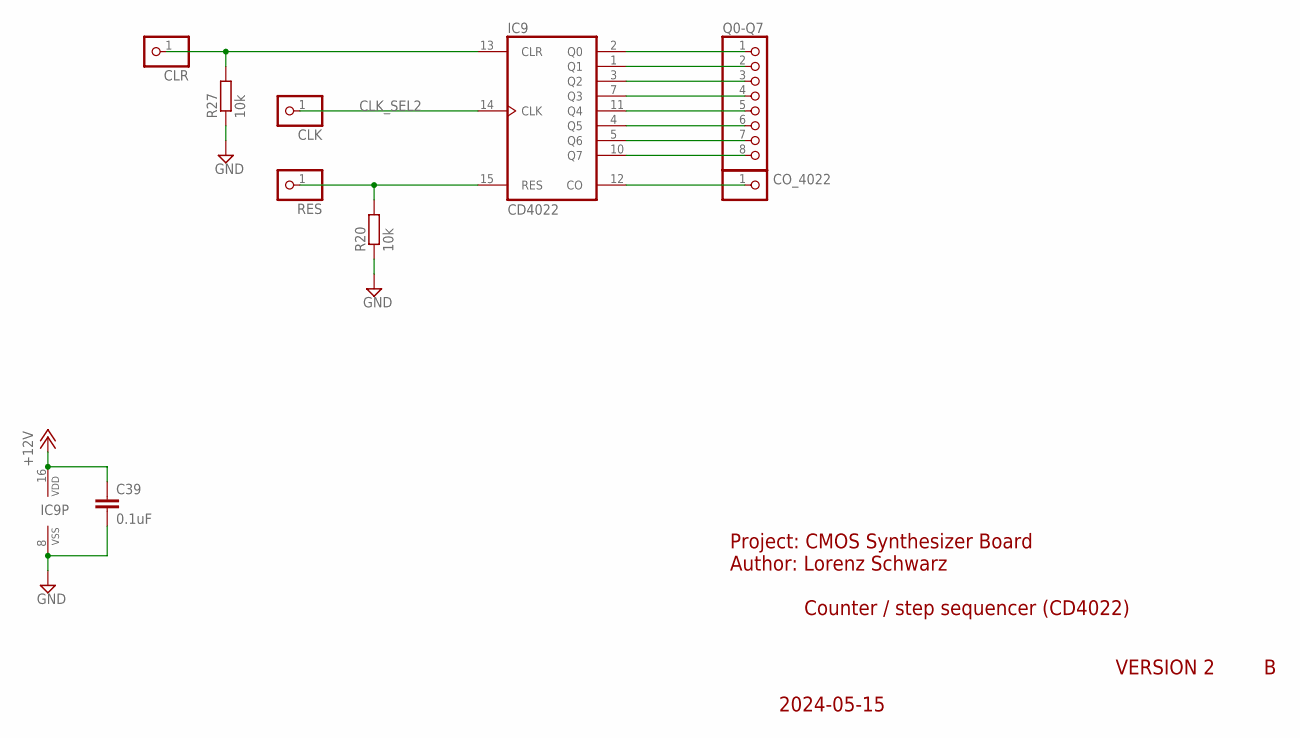
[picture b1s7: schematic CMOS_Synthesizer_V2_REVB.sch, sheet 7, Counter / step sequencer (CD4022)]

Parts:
C39: 0.1uF; C0805
CLK: PINHD-1X1; 1X01
CLR: PINHD-1X1; 1X01
CO_4022: PINHD-1X1; 1X01
IC9: CD4022; DIL16
Q0-Q7: PINHD-1X8_2.54; 1X08
R20, R27: 10k; R0805
RES: PINHD-1X1; 1X01

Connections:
+12V: C39.1, IC9.16 (VDD); also elsewhere on the board
CLK_SEL2: CLK.1, IC9.14 (CLK); also elsewhere on the board
GND: C39.2, IC9.8 (VSS), R20.1, R27.1; also elsewhere on the board
unnamed: IC9.2 (Q0), Q0-Q7.1
unnamed: IC9.1 (Q1), Q0-Q7.2
unnamed: IC9.3 (Q2), Q0-Q7.3
unnamed: IC9.7 (Q3), Q0-Q7.4
unnamed: IC9.11 (Q4), Q0-Q7.5
unnamed: IC9.4 (Q5), Q0-Q7.6
unnamed: IC9.5 (Q6), Q0-Q7.7
unnamed: IC9.10 (Q7), Q0-Q7.8
unnamed: CO_4022.1, IC9.12 (CO)
unnamed: IC9.15 (RES), R20.2, RES.1
unnamed: CLR.1, IC9.13 (CLR), R27.2

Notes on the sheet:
Project: CMOS Synthesizer Board Author: Lorenz Schwarz
Counter / step sequencer (CD4022)
2024-05-15
VERSION 2

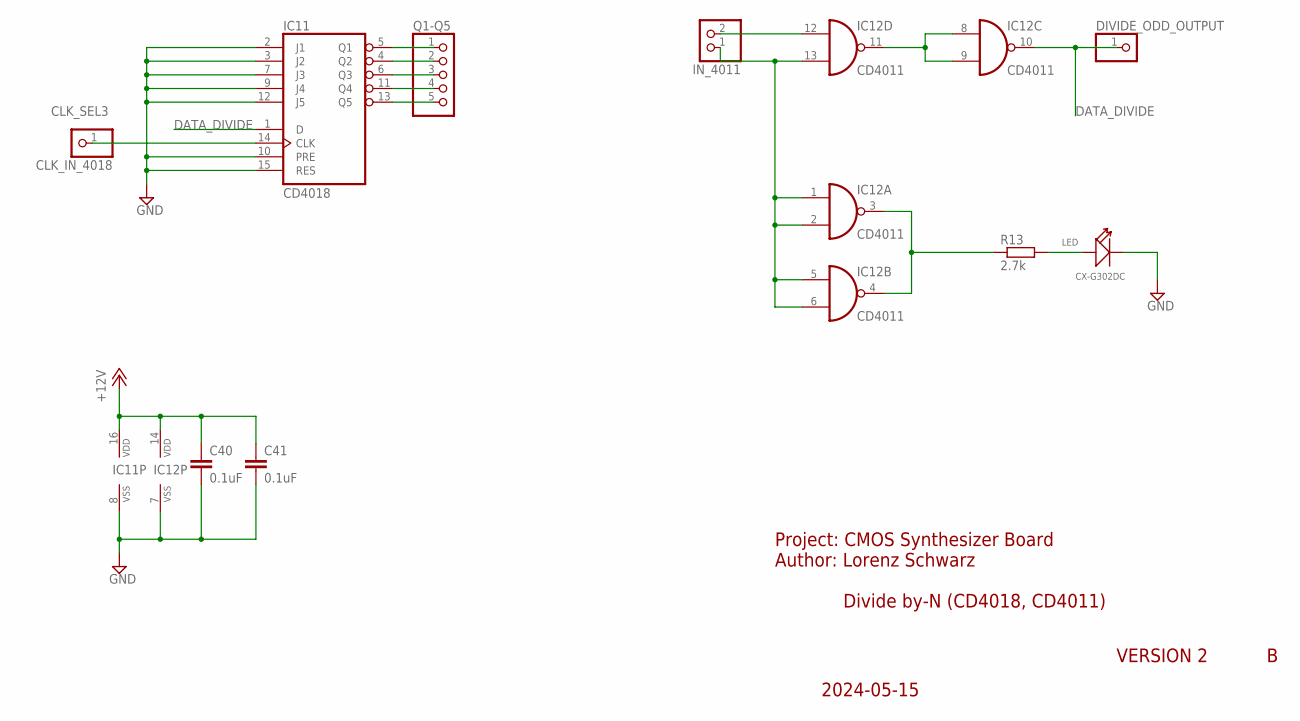
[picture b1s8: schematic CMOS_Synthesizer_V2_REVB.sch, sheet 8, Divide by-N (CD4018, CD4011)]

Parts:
C40, C41: 0.1uF; C0805
CLK_IN_4018: PINHD-1X1; 1X01
DIVIDE_ODD_OUTPUT: PINHD-1X1; 1X01
IC11: CD4018; DIL16
IC12: CD4011; DIL14
IN_4011: PINHD-1X2; 1X02
LED: CX-G302DC; LED2-2.54-D3.0MM
Q1-Q5: PINHD-1X5; 1X05
R13: 2.7k; R0805

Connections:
+12V: C40.1, C41.1, IC11.16 (VDD), IC12.14 (VDD); also elsewhere on the board
CLK_SEL3: CLK_IN_4018.1, IC11.14 (CLK); also elsewhere on the board
DATA_DIVIDE: DIVIDE_ODD_OUTPUT.1, IC11.1 (D), IC12.10 (O)
GND: C40.2, C41.2, IC11.2 (J1), IC11.3 (J2), IC11.7 (J3), IC11.8 (VSS), IC11.9 (J4), IC11.10 (PRE), IC11.12 (J5), IC11.15 (RES), IC12.7 (VSS), LED.K (-); also elsewhere on the board
unnamed: IC12.8 (I0), IC12.9 (I1), IC12.11 (O)
unnamed: IC12.3 (O), IC12.4 (O), R13.1
unnamed: IC12.12 (I0), IN_4011.2
unnamed: LED.A (+), R13.2
unnamed: IC11.5 (Q1), Q1-Q5.1
unnamed: IC11.4 (Q2), Q1-Q5.2
unnamed: IC11.6 (Q3), Q1-Q5.3
unnamed: IC11.11 (Q4), Q1-Q5.4
unnamed: IC11.13 (Q5), Q1-Q5.5
unnamed: IC12.1 (I0), IC12.2 (I1), IC12.5 (I0), IC12.6 (I1), IC12.13 (I1), IN_4011.1

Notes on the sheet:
Project: CMOS Synthesizer Board Author: Lorenz Schwarz
Divide by-N (CD4018, CD4011)
2024-05-15
VERSION 2

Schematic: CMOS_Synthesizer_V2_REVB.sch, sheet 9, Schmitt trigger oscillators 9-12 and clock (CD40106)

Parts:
C18, C19, C20, C21: 1uF; C0805
C23: 22uF; PANASONIC_D
C25, C26, C27, C28, C29: 0.22uF; C0805
C43: 0.1uF; C0805
CLK_OUT: PINHD-1X2; 1X02
IC13: CD40106; DIL14
JP1, JP5, JP6, JP7: PINHD-1X1; 1X01
R15: 2.7k; R0805
RESISTOR1, RESISTOR2, RESISTOR3, RESISTOR4: PINHD-1X2; 1X02
U$14: 100k; POT_VER

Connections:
+12V: C43.1, IC13.14 (VDD); also elsewhere on the board
GND: C18.2, C19.2, C20.2, C21.2, C23.-, C25.2, C26.2, C27.2, C28.2, C29.2, C43.2, IC13.7 (VSS), IC13.13 (I); also elsewhere on the board
LDR1: IC13.8 (O), JP6.1, RESISTOR1.1
LDR2: IC13.6 (O), JP5.1, RESISTOR2.1
LDR3: IC13.10 (O), JP7.1, RESISTOR3.1
LDR4: IC13.4 (O), JP1.1, RESISTOR4.1
LFO: CLK_OUT.1, CLK_OUT.2, IC13.2 (O), R15.2; also elsewhere on the board
unnamed: C23.+, C29.1, IC13.1 (I), U$14.3 (E)
unnamed: R15.1, U$14.1 (A), U$14.2 (S)
unnamed: C21.1, C25.1, IC13.3 (I), RESISTOR4.2
unnamed: C20.1, C26.1, IC13.5 (I), RESISTOR2.2
unnamed: C19.1, C27.1, IC13.9 (I), RESISTOR1.2
unnamed: C18.1, C28.1, IC13.11 (I), RESISTOR3.2

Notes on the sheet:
Project: CMOS Synthesizer Board Author: Lorenz Schwarz
Schmitt trigger oscillators 9-12 and clock (CD40106)
2024-05-15
VERSION 2

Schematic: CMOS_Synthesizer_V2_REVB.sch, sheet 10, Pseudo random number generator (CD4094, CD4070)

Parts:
C44, C45, C46, C47: 0.1uF; C0805
DATA_IN: PINHD-1X1; 1X01
IC15, IC16, IC17: CD4094; DIL16
IC18: CD4070; DIL14
JP2: PINHD-1X2; 1X02
Q1-Q8_OUTPUT, Q9-Q16-OUTPUT, Q17-Q24_OUTPUT: PINHD-1X8; 1X08

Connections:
+12V: C44.1, C45.1, C46.1, C47.1, IC15.1 (STR), IC15.15 (OE), IC15.16 (VDD), IC16.1 (STR), IC16.15 (OE), IC16.16 (VDD), IC17.1 (STR), IC17.15 (OE), IC17.16 (VDD), IC18.14 (VDD); also elsewhere on the board
CLK_SEL1: IC15.3 (CLK), IC16.3 (CLK), IC17.3 (CLK); also elsewhere on the board
GND: C44.2, C45.2, C46.2, C47.2, IC15.8 (VSS), IC16.8 (VSS), IC17.8 (VSS), IC18.5 (I0), IC18.6 (I1), IC18.7 (VSS), IC18.8 (I0), IC18.9 (I1), IC18.12 (I0), IC18.13 (I1); also elsewhere on the board
unnamed: IC15.11 (Q8), IC16.2 (D), Q1-Q8_OUTPUT.8
unnamed: IC16.11 (Q8), IC17.2 (D), Q9-Q16-OUTPUT.8
unnamed: IC17.11 (Q8), Q17-Q24_OUTPUT.8
unnamed: DATA_IN.1, IC15.2 (D), IC18.3 (O)
unnamed: IC15.12 (Q7), Q1-Q8_OUTPUT.7
unnamed: IC15.13 (Q6), Q1-Q8_OUTPUT.6
unnamed: IC15.14 (Q5), Q1-Q8_OUTPUT.5
unnamed: IC15.7 (Q4), Q1-Q8_OUTPUT.4
unnamed: IC15.6 (Q3), Q1-Q8_OUTPUT.3
unnamed: IC15.5 (Q2), Q1-Q8_OUTPUT.2
unnamed: IC15.4 (Q1), Q1-Q8_OUTPUT.1
unnamed: IC16.4 (Q1), Q9-Q16-OUTPUT.1
unnamed: IC16.5 (Q2), Q9-Q16-OUTPUT.2
unnamed: IC16.6 (Q3), Q9-Q16-OUTPUT.3
unnamed: IC16.7 (Q4), Q9-Q16-OUTPUT.4
unnamed: IC16.14 (Q5), Q9-Q16-OUTPUT.5
unnamed: IC16.13 (Q6), Q9-Q16-OUTPUT.6
unnamed: IC16.12 (Q7), Q9-Q16-OUTPUT.7
unnamed: IC17.4 (Q1), Q17-Q24_OUTPUT.1
unnamed: IC17.5 (Q2), Q17-Q24_OUTPUT.2
unnamed: IC17.6 (Q3), Q17-Q24_OUTPUT.3
unnamed: IC17.7 (Q4), Q17-Q24_OUTPUT.4
unnamed: IC17.14 (Q5), Q17-Q24_OUTPUT.5
unnamed: IC17.13 (Q6), Q17-Q24_OUTPUT.6
unnamed: IC17.12 (Q7), Q17-Q24_OUTPUT.7
unnamed: IC18.1 (I0), JP2.2
unnamed: IC18.2 (I1), JP2.1

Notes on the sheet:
Project: CMOS Synthesizer Board Author: Lorenz Schwarz
Pseudo random number generator (CD4094, CD4070)
2024-05-15
VERSION 2

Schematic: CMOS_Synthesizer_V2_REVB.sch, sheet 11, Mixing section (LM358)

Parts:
AUDIO_OUT: PINHD-1X2; 1X02
C34, C48: 0.1uF; C0805
C49, C50, C51, C52, C53: 10uF; PANASONIC_D
DNP: 10uF; PANASONIC_D
GND: PINHD-1X1; 1X01
IC10: LM358; DIL08
J1: MJ-3523-SMT-TR; CUI_MJ-3523-SMT-TR
MIX_1-4: PINHD-1X4; 1X04
R9, R10, R11, R12, R21, R22, R24, R25: 100k; R0805
R23: R-EU_R0805; R0805
U$9, U$10, U$11, U$12, U$13: 100k; POT_VER

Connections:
+12V: C48.1, IC10.8 (V+), R9.2; also elsewhere on the board
GND: AUDIO_OUT.2, C34.2, C48.2, DNP.-, GND.1, IC10.4 (V-), J1.1, R10.1, U$9.1 (A), U$10.1 (A), U$11.1 (A), U$12.1 (A), U$13.1 (A); also elsewhere on the board
unnamed: C49.+, U$9.2 (S)
unnamed: C50.+, U$10.2 (S)
unnamed: IC10.6 (-IN), R11.1, R12.1, R21.1, R22.1, R23.2
unnamed: IC10.2 (-IN), R24.1, R25.2
unnamed: IC10.7 (OUT), R23.1, R24.2
unnamed: C53.+, IC10.1 (OUT), R25.1
unnamed: C51.+, U$11.2 (S)
unnamed: C52.+, U$12.2 (S)
unnamed: C52.-, R22.2
unnamed: C51.-, R21.2
unnamed: C50.-, R12.2
unnamed: C49.-, R11.2
unnamed: MIX_1-4.4, U$9.3 (E)
unnamed: MIX_1-4.3, U$10.3 (E)
unnamed: MIX_1-4.2, U$11.3 (E)
unnamed: MIX_1-4.1, U$12.3 (E)
unnamed: C53.-, U$13.3 (E)
unnamed: AUDIO_OUT.1, J1.2, U$13.2 (S)
REF: C34.1, DNP.+, IC10.3 (+IN), IC10.5 (+IN), R9.1, R10.2

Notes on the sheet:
Project: CMOS Synthesizer Board Author: Lorenz Schwarz
Mixing section (LM358)
2024-05-15
VERSION 2

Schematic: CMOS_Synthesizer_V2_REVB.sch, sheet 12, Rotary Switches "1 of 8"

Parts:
1, 2, 3, 4, 5, 6, 7, 8: PINHD-1X1; 1X01
EXT_CLK01: PINHD-1X2; 1X02
EXT_CLK_02: PINHD-1X2; 1X02
GND_CON: PINHD-1X2; 1X02
S9, S10, S11: ROTARY_SWITCH; ROTARY

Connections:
CLK_SEL1: S9.A; also elsewhere on the board
CLK_SEL2: S10.A; also elsewhere on the board
CLK_SEL3: S11.A; also elsewhere on the board
DIV4: 6.1, S9.6, S10.6, S11.6; also elsewhere on the board
GND: GND_CON.1, GND_CON.2; also elsewhere on the board
LFO: 5.1, S9.5, S10.5, S11.5; also elsewhere on the board
OSC1: 1.1, S9.1, S10.1, S11.1; also elsewhere on the board
OSC2: 2.1, S9.2, S10.2, S11.2; also elsewhere on the board
OSC3: 3.1, S9.3, S10.3, S11.3; also elsewhere on the board
OSC4: 4.1, S9.4, S10.4, S11.4; also elsewhere on the board
SIG7: 7.1, EXT_CLK01.1, EXT_CLK01.2, S9.7, S10.7, S11.7
SIG8: 8.1, EXT_CLK_02.1, EXT_CLK_02.2, S9.8, S10.8, S11.8

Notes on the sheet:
Project: CMOS Synthesizer Board Author: Lorenz Schwarz
2024-05-15
Rotary switches
VERSION 2

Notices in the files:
README.md:
Original materials in this repository (schematics, board layouts, mechanical drawings, written documentation, and photographs by the author) are licensed under the [Creative Commons Attribution 4.0 International license (CC BY 4.0)](https://creativecommons.org/licenses/by/4.0/). The full legal text is included in [`LICENSE.md`](./LICENSE.md).
Photographs by third parties.** Images whose filenames carry a `_c_` credit (e.g., `IMG_5902_c_Hongyu_Guo.webp`, `cmos-synth-edit_c_Tobias_Ehrhardt.webp`, `bowed-electrons-khwa-ttu-2024-trilogy-02_c_Clive_Pringle.webp`, `sae-cape-town-2
